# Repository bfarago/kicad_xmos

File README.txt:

VERSION V1.1
FB236: XUF216-512-FB236, XE216-512-FB236
FB217: xs1-a16a-128-fb217
FB96: xs1-a8a-64-fb96
TQ128: XE216-512-TQ128
TQ64: XL208-256-TQ64

0) Simply open .pro project files by kicad, and take a look...
The examples\demo_preview  project contains all of the footprints.

If you want to create some design with the library:
1) COPY FILES TO A COMMON PLACE 
Note: different kiCad installations can use different folders, I guess. 
 xmos.lib  and .dcm file can be placed to  kicad\share\library
 xmos.pretty folder can be in  kicad\share\modules
 But you can leave everything in the project folder of course...

2) SETUP
 schematic and pcb editor preferencies, basically to search this libs.
 If you placed the files to global folder, there is an option to setup as global
 config (in this case all of the new projects will find these files automaticaly).
 For first sight, I suggest to use as project specific libs...
 In case of trial config, you can leave everything in one folder, but in a
 new project you have to change your kicad settings of course...
 
3) DEMOs
try out demo project.
FB96 or BGA96 is a 96 pins BGA package for xmos products.
FB217 or BGA217 is a 217 pins BGA with 0.8mm pitch ~0.4mm pad size.
Exact sizes, and thermal pad/gnd plane design was based by the official xmos documentation.

Each xmos schematic component connects multiple pins to one electrical net by
coordinates. Check out the lib editor, what I am talking about.. :)
It was mentioned by some forum post, and I think it is a usable method. 
At the center of the bga chip theres a couple of GND balls. I pinout each, but only
one is visible in schematic editor. When you connect gnd power component to this point,
kicad will connect each. (KiCad has no pin-to-net net-to-pad ability).

TODO:
 -fix pin directions (kicad able to define, but it is a pain in the ass to use it realy)
 -fix pin positions in schematic. It would be nice to have same pins in same coordinate..
 -demo projects schematics need to be updated, because of the pin positions has been changed on component.

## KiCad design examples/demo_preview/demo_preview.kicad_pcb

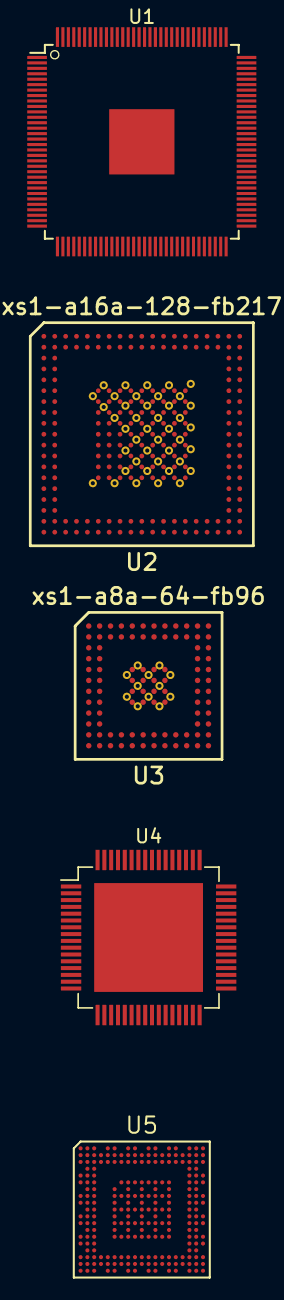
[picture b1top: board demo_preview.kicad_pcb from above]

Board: 2 copper layers, 5 parts (0 on the bottom side), 12 nets, no tracks yet.

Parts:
U1: XE216-512-TQ128; TQFP-128_14x14mm_Pitch0.4mm_Len1.45mm_thermalpad
U2: xs1-a16a-128-fb217; BGA217
U3: xs1-a8a-64-fb96; BGA96
U4: XU208-256-TQ64; TQFP-64_1EP_10x10mm_Pitch0.5mm
U5: XUF216-512-FB236; FB236

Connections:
PGND: U2.V1, U2.V2, U2.V4, U2.W4, U3.L1, U3.L2, U3.M4
SW1: U2.R1, U2.R2, U2.T1, U3.J1, U3.J2
SW2: U2.V6, U2.W6
VCORE: U2.T2, U2.U1, U2.U2, U3.K1, U3.K2
VDD: U1.16, U1.17, U1.24, U1.35, U1.40, U1.49, U1.58, U1.61, U1.72, U1.80, U1.81, U1.87, U1.101, U1.102, U1.120
VDD1V8: U2.V5, U2.W5
VDDIO: U2.V3, U2.W3, U3.L3, U3.M3
VDDIOL: U1.5, U1.13, U1.19, U1.29, U1.42
VDDIOR: U1.55, U1.67, U1.77, U1.83, U1.92
VDDIOT: U1.110, U1.111
VSS: U2.G6, U2.G7, U2.G8, U2.G9, U2.G10, U2.G11, U2.G12, U2.G13, U2.G14, U2.H6, U2.H7, U2.H8, U2.H9, U2.H10, U2.H11, U2.H12, U2.H13, U2.H14, U2.J7, U2.J8, U2.J9, U2.J10, U2.J11, U2.J12, U2.J13, U2.J14, U2.K8, U2.K9, U2.K10, U2.K11, U2.K12, U2.K13, U2.K14, U2.L8, U2.L9, U2.L10, U2.L11, U2.L12, U2.L13, U2.L14, U2.M8, U2.M9, U2.M10, U2.M11, U2.M12, U2.M13, U2.M14, U2.N8, U2.N9, U2.N10, U2.N11, U2.N12, U2.N13, U2.N14, U2.P6, U2.P7, U2.P8, U2.P9, U2.P10, U2.P11, U2.P12, U2.P13, U2.P14, U3.E5, U3.E6, U3.E7, U3.E8, U3.F5, U3.F6, U3.F7, U3.F8, U3.G5, U3.G6, U3.G7, U3.G8, U3.H5, U3.H6, U3.H7, U3.H8
VSUP: U2.P2, U2.W1, U2.W2, U3.H2, U3.M1, U3.M2

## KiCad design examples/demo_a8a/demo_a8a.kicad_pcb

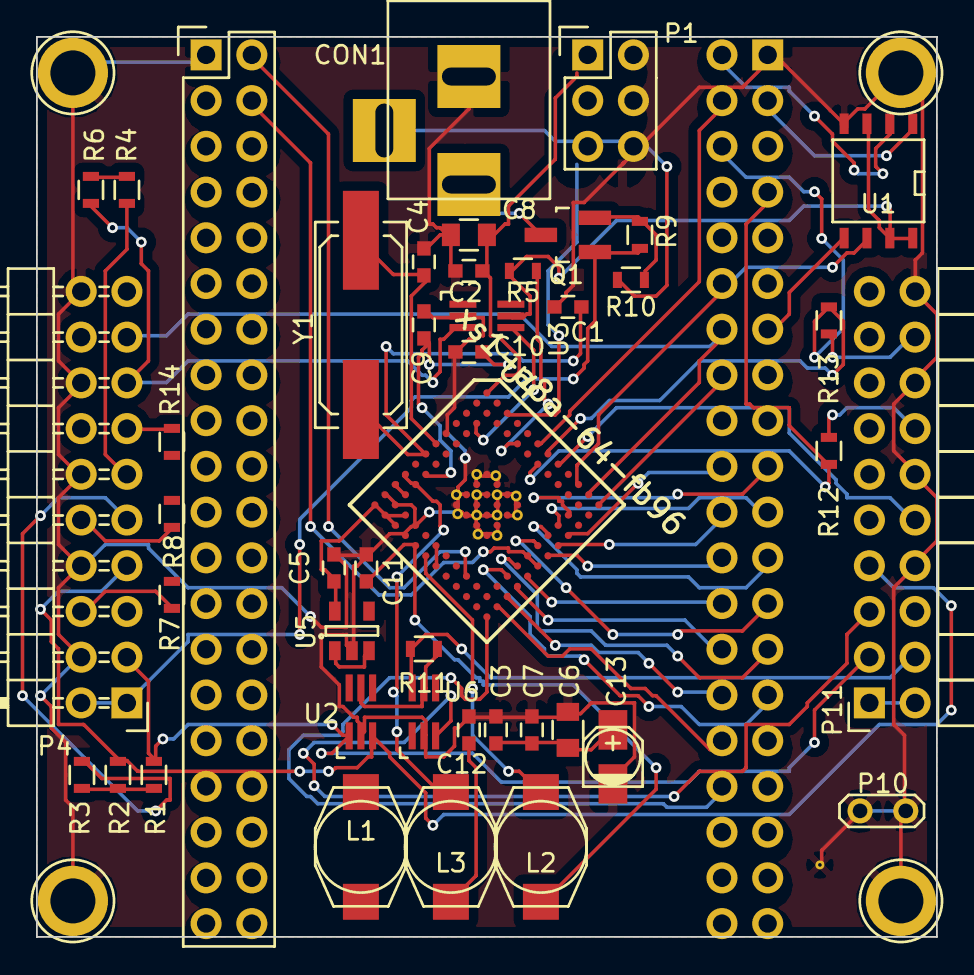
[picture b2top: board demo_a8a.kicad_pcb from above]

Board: 2 copper layers, 50.0 x 50.0 mm, 50 parts (1 on the bottom side), 78 nets.

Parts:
C1, C4: 33p; C_0603
C2, C3, C7, C9, C10, C11, C12: 100n; C_0603
C5: 4u7; C_0603
C6, C8: 10u; C_0805
C13: CP_Small; c_elec_3x5.3
CON1: BARREL_JACK
L1, L2, L3: 4u7; SELF-WE-PD3S
P1: CONN_02X03; Pin_Header_Straight_2x03
P2, P3: CONN_02X20; Pin_Header_Straight_2x20
P4: XLinkIn; Pin_Header_Angled_2x10
P5: Pillar
P6, P7, P8, P9: SCREW; screw
P10: clip; TESTPOINT
P11: XLinkOut; Socket_Strip_Angled_2x10
Q1: ntr4101 P; SOT-23_Handsoldering
R1, R2, R3, R4, R6: 47K; R_0603
R5: 10k; R_0603
R7, R8, R12, R13, R14: 33R; R_0603
R9, R11: 47k; R_0603
R10: 1k; R_0603
U1: w25x40cl; SOIC-8-N
U2, U3: NC7WZ17; SC-70-6_Handsoldering
U4: xs1-a8a-64-fb96; BGA96
U5: NCP699SN33; SOT-23-5
U6: NC7SZ157; SC-70-6_Handsoldering
Y1: 25M; Q_49U3HMS

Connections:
+3.3VADC: C2.1, C8.1, L1.1, P1.1, U4.A1
/D0: P3.2, U1.2, U4.A5
/D1: P3.3, R5.1, U1.1, U4.B5
/D2: P3.4, U4.A6
/D3: P3.5, U4.B6
/D8: P3.10, U4.A9
/D9: P3.11, U4.B9
/D10: P3.12, U1.6, U4.A10
/D11: P3.13, U1.5, U4.B10
/D14: P3.16, U4.A12
/D15: P3.17, U4.B12
/D20: P3.22, U4.E12
/D21: P3.23, U4.E11
/D22: P3.24, U4.F12
/D23: P3.25, U4.F11
/D24: P3.26, U4.H12
/D25: P3.27, U4.H11
/D26: P3.28, U4.J12
/D27: P3.29, U4.J11
/D28: P3.30, U4.K12
/D29: P3.31, U4.K11
/D30: P3.32, U4.L12
/D31: P3.33, U4.L11
/D32: P3.34, U4.M12
/D33: P3.35, U4.M11
/D34: P3.36, U4.M8
/D35: P3.37, U4.L8
/D36: P3.38, U4.M10
/D37: P3.39, U4.L10
/D38: P3.40, U4.M9
/D39: P2.2, U4.L9
/D43: P2.3, U4.L7
/D70: P2.4, U4.G11, U4.G12
/MSEL: U2.6, U4.L6, U4.M7
/XADC0: P1.3, U4.A2
/XADC1: P1.2, U4.B2
/XADC2: P1.5, U4.A3
/XADC3: P1.4, U4.B3
/XTCK: U3.6, U4.C1
/XTMS: U2.4, U4.D1
/pwr/INUNREG: P4.1, P4.2, Q1.1, R9.1
/pwr/OUTUNREG: CON1.1, P11.1, P11.2, Q1.3, U5.1, U5.3
/xlinkin1/LINK0D: P3.20, P4.14, U4.D12
/xlinkin1/LINK0U: P3.19, R8.1, U4.C11
/xlinkin1/LINK1D: P3.21, P4.18, U4.D11
/xlinkin1/LINK1U: P3.18, R7.1, U4.C12
/xlinkin1/TCK: P4.9, P11.9, R3.2, U3.1
/xlinkin1/TDI: P4.5, U4.D2
/xlinkin1/TDO: P4.13, R14.1
/xlinkin1/TMS: P4.7, P11.7, R2.2, U2.3
/xlinkin1/UARTRX: P3.14, P4.17, U4.A11
/xlinkin1/UARTTX: P3.15, P4.19, U4.B11
/xlinkin1/XLi0u: P4.10, R8.2
/xlinkin1/XLi1u: P4.6, R7.2
/xlinkin1/~DBG: P4.11, P11.11, R6.1, U4.E2
/xlinkin1/~RST: P4.15, P11.15, R4.2, U3.3
/xlinkin1/~TRST: P4.3, P11.3, R1.2, U2.1
/xlinkout1/ELo0d: P11.14, R12.2
/xlinkout1/ELo1d: P11.18, R13.2
/xlinkout1/ELoTDO: P11.13, U6.1
/xlinkout1/LINK0D: P3.7, R12.1, U4.B7
/xlinkout1/LINK0U: P3.8, P11.10, U4.A8
/xlinkout1/LINK1D: P3.6, R13.1, U4.A7
/xlinkout1/LINK1U: P3.9, P11.6, U4.B8
/xlinkout1/TDI: P11.5, U4.B1, U6.3
/xlinkout1/~PRESENT: P11.4, R11.2, U6.6
/~XRST: U3.4, U4.C2
GND: C1.2, C2.2, C3.2, C4.2, C5.2, C6.2, C7.2, C8.2, C9.2, C10.2, C11.2, C12.2, C13.2, CON1.2, P1.6, P2.1, P3.1, P4.4, P4.8, P4.12, P4.16, P4.20, P5.1, P6.1, P7.1, P8.1, P9.1, P10.1, P11.8, P11.12, P11.16, P11.20, U1.4, U2.2, U3.2, U4.E1, U4.E5, U4.E6, U4.E7, U4.E8, U4.F5, U4.F6, U4.F7, U4.F8, U4.G5, U4.G6, U4.G7, U4.G8, U4.GND, U4.H5, U4.H6, U4.H7, U4.H8, U4.L1, U4.L2, U4.L4, U4.M4, U5.2, U6.2
unnamed: C1.1, U4.G1, Y1.1
unnamed: C4.1, U4.F1, Y1.2
unnamed: C11.1, L2.1, U4.M5
unnamed: CON1.3, R10.2
unnamed: L2.2, U4.M6
unnamed: Q1.2, R9.2, R10.1
unnamed: R14.2, U6.4
SW1: L3.2, U4.J1, U4.J2
VCC: C3.1, C5.1, C6.1, C7.1, C9.1, C10.1, C13.1, L1.2, R1.1, R2.1, R3.1, R4.1, R5.2, R6.2, R11.1, U1.3, U1.7, U1.8, U2.5, U3.5, U4.H2, U4.L3, U4.M1, U4.M2, U4.M3, U5.5, U6.5
VCORE: C12.1, L3.1, U4.K1, U4.K2

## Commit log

2016-08-30 Public release - initial
2016-09-04 Added common folder, common sub-schematics. Fixed user spec. library path, to be relative to the projects.
2016-09-10 PCIe_FootprintWizard inital version
2017-06-18 project level lib added
2017-06-19 FB236 added
2017-06-19 fb236 added.
2017-06-19 just fix one typo.
2019-03-11 re-save with KiCad 5.0.2
2019-03-11 XMOS XE216-512-TQ128: correctly wire up pins
    The changes are based on the XE216-512-TQ128 datasheet,
    version 1.16 (2018-09-05).
